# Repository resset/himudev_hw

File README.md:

# hIMUdev

hIMUdev is a RISC-V powered IMU evaluation board. Current version (1.0) hasn't been tested yet, so expect updates and changes.

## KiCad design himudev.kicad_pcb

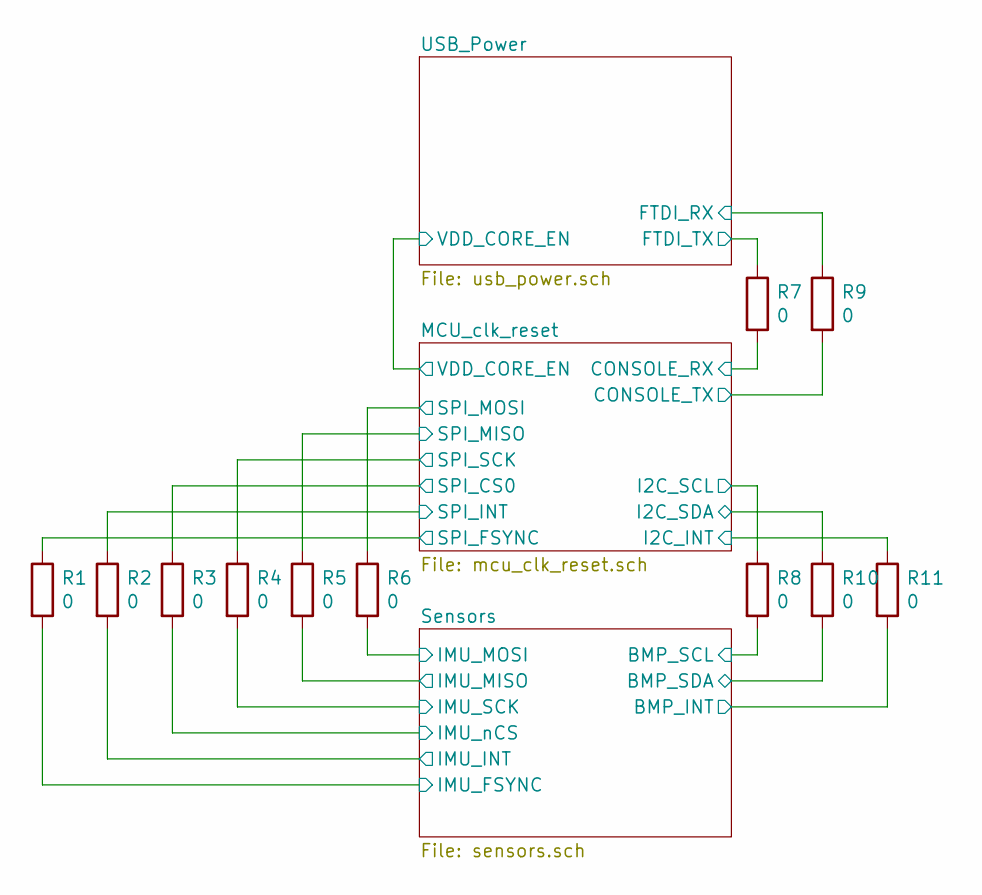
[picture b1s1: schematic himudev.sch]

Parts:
R1, R2, R3, R4, R5, R6, R7, R8, R9, R10, R11: 0; R_0603_1608Metric_Pad1.05x0.95mm_HandSolder

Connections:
/MCU_clk_reset/CONSOLE_RX: R7.2; also elsewhere on the board
/MCU_clk_reset/CONSOLE_TX: R9.2; also elsewhere on the board
/MCU_clk_reset/I2C_INT: R11.1; also elsewhere on the board
/MCU_clk_reset/I2C_SCL: R8.1; also elsewhere on the board
/MCU_clk_reset/I2C_SDA: R10.1; also elsewhere on the board
/MCU_clk_reset/SPI_CS0: R3.1; also elsewhere on the board
/MCU_clk_reset/SPI_FSYNC: R1.1; also elsewhere on the board
/MCU_clk_reset/SPI_INT: R2.1; also elsewhere on the board
/MCU_clk_reset/SPI_MISO: R5.1; also elsewhere on the board
/MCU_clk_reset/SPI_MOSI: R6.1; also elsewhere on the board
/MCU_clk_reset/SPI_SCK: R4.1; also elsewhere on the board
/Sensors/BMP_INT: R11.2; also elsewhere on the board
/Sensors/BMP_SCL: R8.2; also elsewhere on the board
/Sensors/BMP_SDA: R10.2; also elsewhere on the board
/Sensors/IMU_FSYNC: R1.2; also elsewhere on the board
/Sensors/IMU_INT: R2.2; also elsewhere on the board
/Sensors/IMU_MISO: R5.2; also elsewhere on the board
/Sensors/IMU_MOSI: R6.2; also elsewhere on the board
/Sensors/IMU_SCK: R4.2; also elsewhere on the board
/Sensors/IMU_nCS: R3.2; also elsewhere on the board
/USB_Power/FTDI_RX: R9.1; also elsewhere on the board
/USB_Power/FTDI_TX: R7.1; also elsewhere on the board

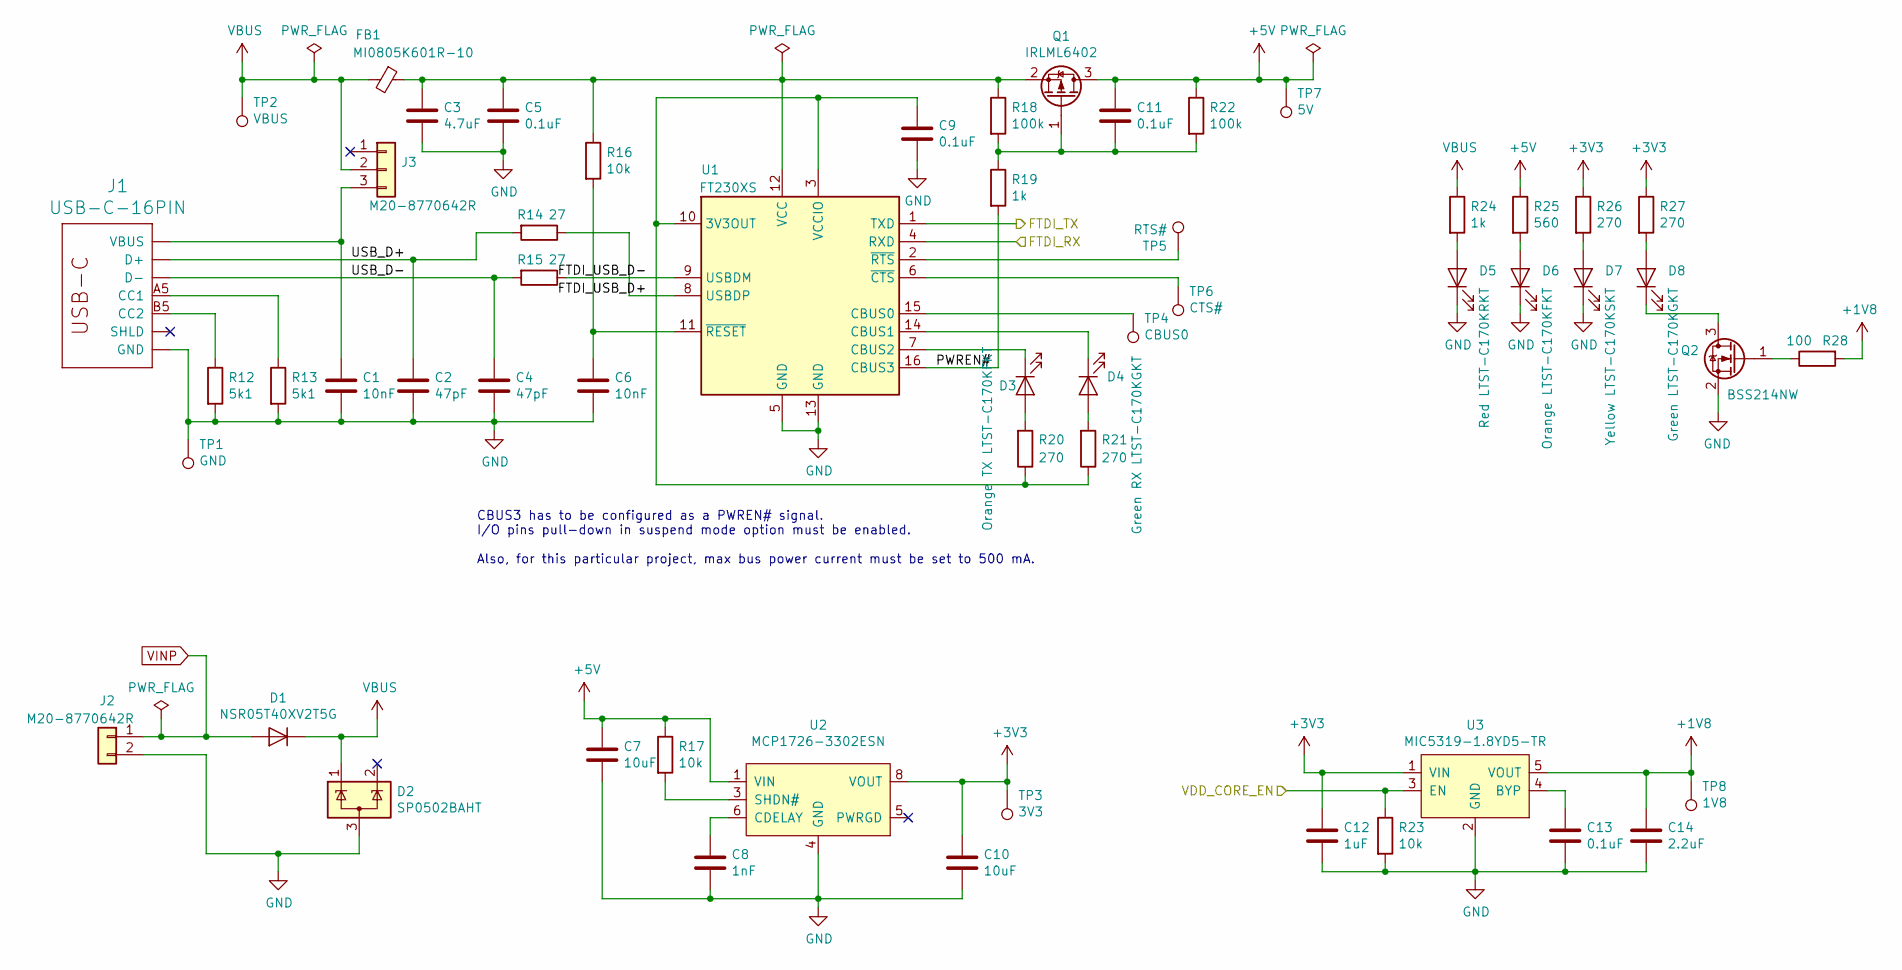
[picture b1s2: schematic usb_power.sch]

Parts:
C1, C6: 10nF; C_0603_1608Metric_Pad1.05x0.95mm_HandSolder
C2, C4: 47pF; C_0603_1608Metric_Pad1.05x0.95mm_HandSolder
C3: 4.7uF; C_0603_1608Metric_Pad1.05x0.95mm_HandSolder
C5, C9, C11, C13: 0.1uF; C_0603_1608Metric_Pad1.05x0.95mm_HandSolder
C7, C10: 10uF; C_0603_1608Metric_Pad1.05x0.95mm_HandSolder
C8: 1nF; C_0603_1608Metric_Pad1.05x0.95mm_HandSolder
C12: 1uF; C_0603_1608Metric_Pad1.05x0.95mm_HandSolder
C14: 2.2uF; C_0603_1608Metric_Pad1.05x0.95mm_HandSolder
D1: NSR05T40XV2T5G; D_SOD-523
D2: SP0502BAHT; SOT-23
D3: Orange TX LTST-C170KFKT; LED_0805_2012Metric_Pad1.15x1.40mm_HandSolder
D4: Green RX LTST-C170KGKT; LED_0805_2012Metric_Pad1.15x1.40mm_HandSolder
D5: Red LTST-C170KRKT; LED_0805_2012Metric_Pad1.15x1.40mm_HandSolder
D6: Orange LTST-C170KFKT; LED_0805_2012Metric_Pad1.15x1.40mm_HandSolder
D7: Yellow LTST-C170KSKT; LED_0805_2012Metric_Pad1.15x1.40mm_HandSolder
D8: Green LTST-C170KGKT; LED_0805_2012Metric_Pad1.15x1.40mm_HandSolder
FB1: MI0805K601R-10; R_0805_2012Metric_Pad1.15x1.40mm_HandSolder
J1: USB-C-16PIN; USB-C-COM-15111
J2: M20-8770642R; PinHeader_1x02_P2.54mm_Vertical_SMD_Pin1Left
J3: M20-8770642R; PinHeader_1x03_P2.54mm_Vertical_SMD_Pin1Left
Q1: IRLML6402; SOT-23
Q2: BSS214NW; SOT-323_SC-70
R12, R13: 5k1; R_0603_1608Metric_Pad1.05x0.95mm_HandSolder
R14, R15: 27; R_0603_1608Metric_Pad1.05x0.95mm_HandSolder
R16, R17, R23: 10k; R_0603_1608Metric_Pad1.05x0.95mm_HandSolder
R18, R22: 100k; R_0603_1608Metric_Pad1.05x0.95mm_HandSolder
R19, R24: 1k; R_0603_1608Metric_Pad1.05x0.95mm_HandSolder
R20, R21, R26, R27: 270; R_0603_1608Metric_Pad1.05x0.95mm_HandSolder
R25: 560; R_0603_1608Metric_Pad1.05x0.95mm_HandSolder
R28: 100; R_0603_1608Metric_Pad1.05x0.95mm_HandSolder
TP1: GND; TestPoint_Pad_D1.5mm
TP2: VBUS; TestPoint_Pad_D1.5mm
TP3: 3V3; TestPoint_Pad_D1.5mm
TP4: CBUS0; TestPoint_Pad_D1.5mm
TP5: RTS#; TestPoint_Pad_D1.5mm
TP6: CTS#; TestPoint_Pad_D1.5mm
TP7: 5V; TestPoint_Pad_D1.5mm
TP8: 1V8; TestPoint_Pad_D1.5mm
U1: FT230XS; SSOP-16_3.9x4.9mm_P0.635mm
U2: MCP1726-3302ESN; SOIC-8_3.9x4.9mm_P1.27mm
U3: MIC5319-1.8YD5-TR; TSOT-23-5

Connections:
+1V8: C14.1, R28.2, TP8.1, U3.5 (VOUT); also elsewhere on the board
+3V3: C10.1, C12.1, R26.1, R27.1, TP3.1, U2.7 (VOUT), U2.8 (VOUT), U3.1 (VIN); also elsewhere on the board
+5V: C7.1, C11.1, Q1.3 (D), R17.1, R22.1, R25.1, TP7.1, U2.1 (VIN), U2.2 (VIN); also elsewhere on the board
/MCU_clk_reset/VDD_CORE_EN: R23.1, U3.3 (EN); also elsewhere on the board
/USB_Power/FTDI_RX: U1.4 (RXD); also elsewhere on the board
/USB_Power/FTDI_TX: U1.1 (TXD); also elsewhere on the board
/USB_Power/FTDI_USB_D+: R14.1, U1.8 (USBDP)
/USB_Power/FTDI_USB_D-: R15.1, U1.9 (USBDM)
/USB_Power/PWREN#: R19.2, U1.16 (CBUS3)
/USB_Power/USB_D+: C2.1, J1.A6 (D+), J1.B6 (D+), R14.2
/USB_Power/USB_D-: C4.1, J1.A7 (D-), J1.B7 (D-), R15.2
GND: C1.2, C2.2, C3.2, C4.2, C5.2, C6.2, C7.2, C8.2, C9.2, C10.2, C12.2, C13.2, C14.2, D2.3 (A), D5.1 (K), D6.1 (K), D7.1 (K), J1.GND, J1.GND2 (GND), J2.2, Q2.2 (S), R12.2, R13.2, R23.2, TP1.1, U1.5 (GND), U1.13 (GND), U2.4 (GND), U3.2 (GND); also elsewhere on the board
unnamed: C1.1, J1.VBUS1 (VBUS), J1.VBUS2 (VBUS), J3.3
unnamed: C3.1, C5.1, FB1.1, Q1.2 (S), R16.1, R18.1, U1.12 (VCC)
unnamed: C6.1, R16.2, U1.11 (~RESET)
unnamed: C8.1, U2.6 (CDELAY)
unnamed: C9.1, R20.1, R21.1, U1.3 (VCCIO), U1.10 (3V3OUT)
unnamed: C11.2, Q1.1 (G), R18.2, R19.1, R22.2
unnamed: C13.1, U3.4 (BYP)
unnamed: D3.1 (K), U1.7 (CBUS2)
unnamed: D3.2 (A), R20.2
unnamed: D4.1 (K), U1.14 (CBUS1)
unnamed: D4.2 (A), R21.2
unnamed: D5.2 (A), R24.2
unnamed: D6.2 (A), R25.2
unnamed: D7.2 (A), R26.2
unnamed: D8.1 (K), Q2.3 (D)
unnamed: D8.2 (A), R27.2
unnamed: J1.A5 (CC1), R13.1
unnamed: J1.B5 (CC2), R12.1
unnamed: J1.SHLD1 (SHLD), J1.SHLD2 (SHLD), J1.SHLD3 (SHLD), J1.SHLD4 (SHLD), J1.SHLD5 (SHLD), J1.SHLD6 (SHLD), J1.SHLD7 (SHLD), J1.SHLD8 (SHLD)
unnamed: Q2.1 (G), R28.1
unnamed: R17.2, U2.3 (SHDN#)
unnamed: TP4.1, U1.15 (CBUS0)
unnamed: TP5.1, U1.2 (~RTS)
unnamed: TP6.1, U1.6 (~CTS)
VBUS: D1.1 (K), D2.1 (K), FB1.2, J3.2, R24.1, TP2.1; also elsewhere on the board
VINP: D1.2 (A), J2.1; also elsewhere on the board

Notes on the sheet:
CBUS3 has to be configured as a PWREN# signal. I/O pins pull-down in suspend mode option must be enabled. Also, for this particular project, max bus power current must be set to 500 mA.

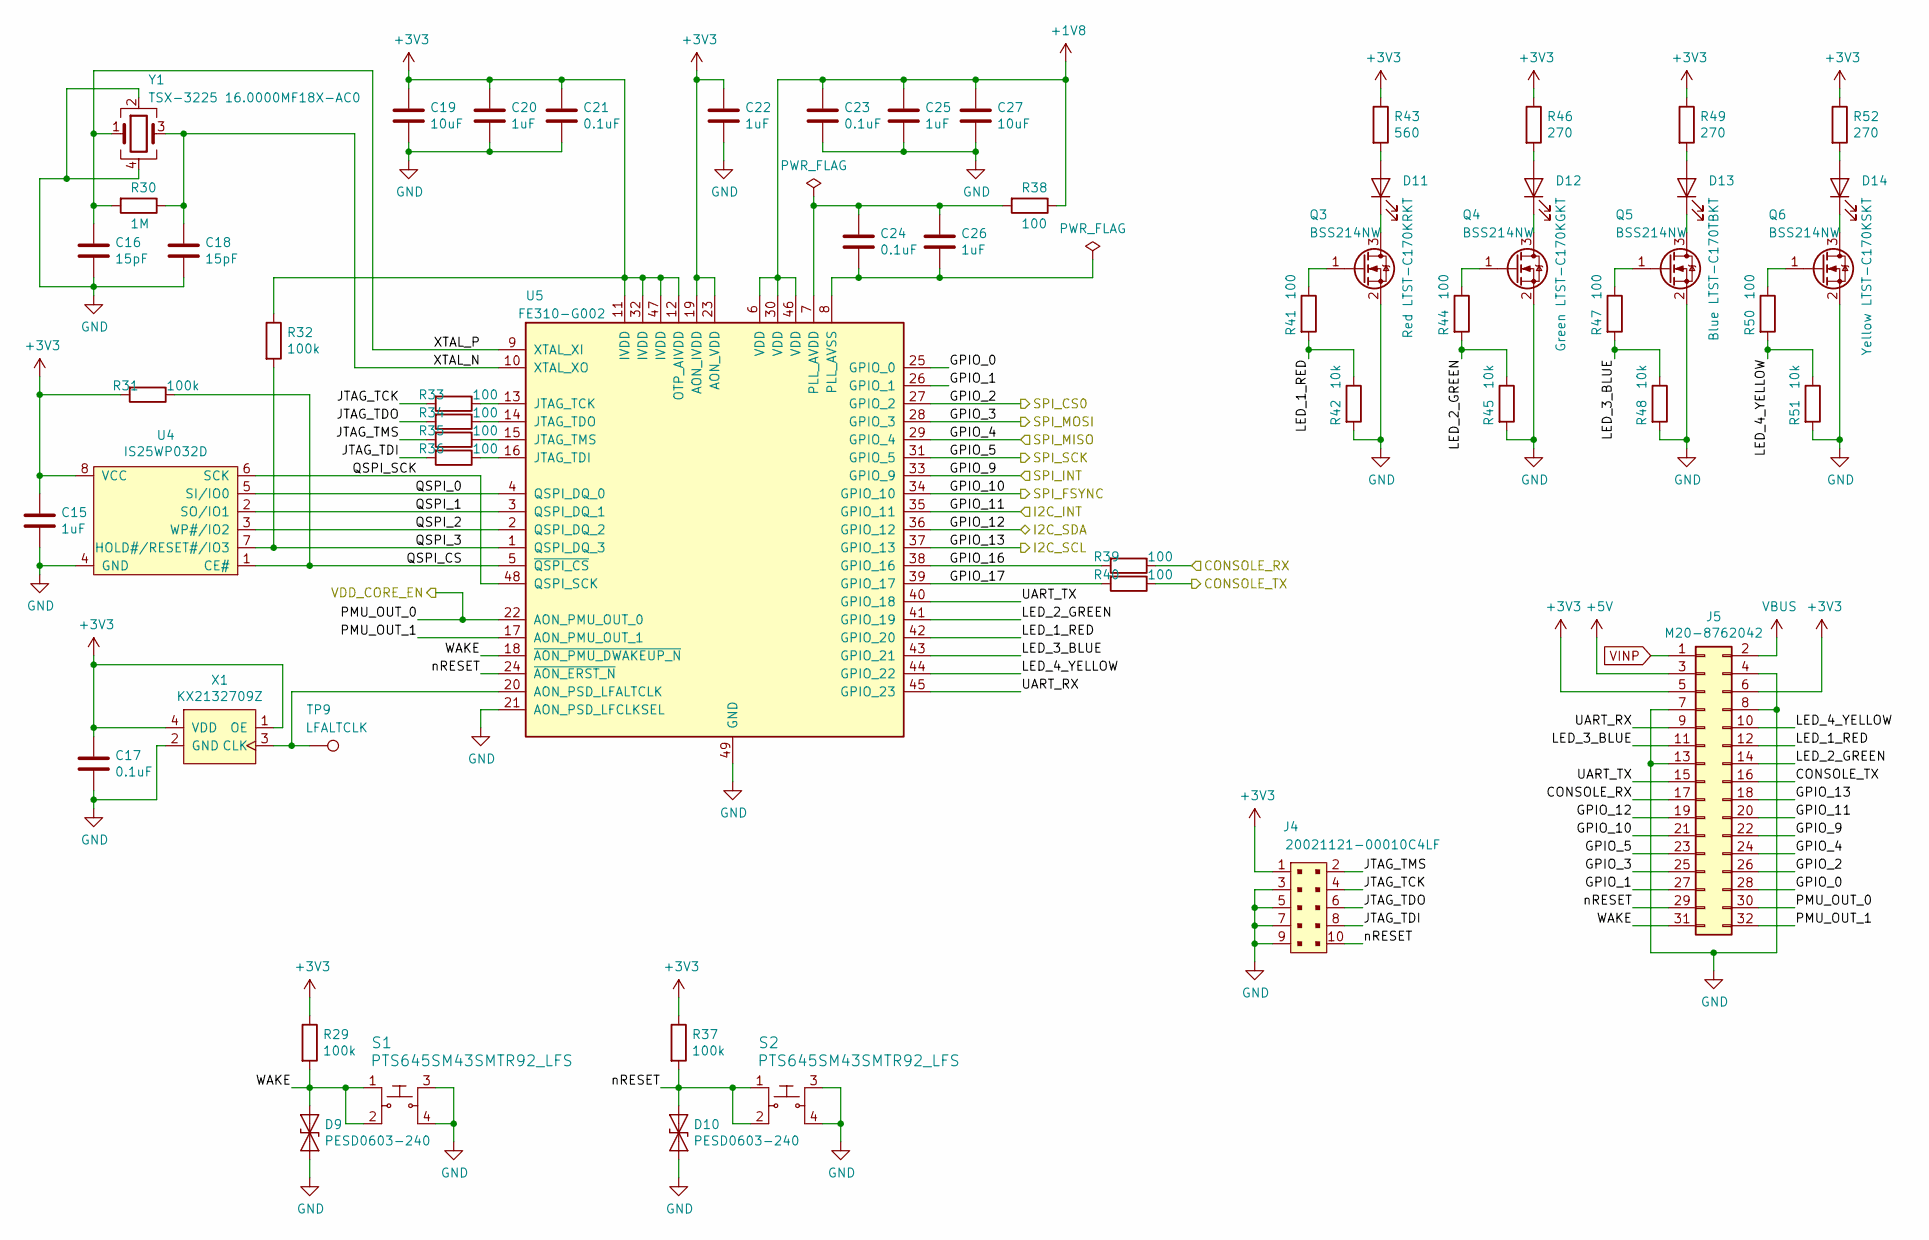
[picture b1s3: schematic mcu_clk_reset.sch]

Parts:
C15, C20, C22, C25, C26: 1uF; C_0603_1608Metric_Pad1.05x0.95mm_HandSolder
C16, C18: 15pF; C_0603_1608Metric_Pad1.05x0.95mm_HandSolder
C17, C21, C23, C24: 0.1uF; C_0603_1608Metric_Pad1.05x0.95mm_HandSolder
C19, C27: 10uF; C_0603_1608Metric_Pad1.05x0.95mm_HandSolder
D9, D10: PESD0603-240; D_0603_1608Metric_Pad1.05x0.95mm_HandSolder
D11: Red LTST-C170KRKT; LED_0805_2012Metric_Pad1.15x1.40mm_HandSolder
D12: Green LTST-C170KGKT; LED_0805_2012Metric_Pad1.15x1.40mm_HandSolder
D13: Blue LTST-C170TBKT; LED_0805_2012Metric_Pad1.15x1.40mm_HandSolder
D14: Yellow LTST-C170KSKT; LED_0805_2012Metric_Pad1.15x1.40mm_HandSolder
J4: 20021121-00010C4LF; PinHeader_2x5_P1.27mm; MPN 20021121-00010C4LF; Digi-Key_PN 609-3695-1-ND
J5: M20-8762042; PinHeader_2x16_P2.54mm_Vertical_SMD
Q3, Q4, Q5, Q6: BSS214NW; SOT-323_SC-70
R29, R31, R32, R37: 100k; R_0603_1608Metric_Pad1.05x0.95mm_HandSolder
R30: 1M; R_0603_1608Metric_Pad1.05x0.95mm_HandSolder
R33, R34, R35, R36, R38, R39, R40, R41, R44, R47, R50: 100; R_0603_1608Metric_Pad1.05x0.95mm_HandSolder
R42, R45, R48, R51: 10k; R_0603_1608Metric_Pad1.05x0.95mm_HandSolder
R43: 560; R_0603_1608Metric_Pad1.05x0.95mm_HandSolder
R46, R49, R52: 270; R_0603_1608Metric_Pad1.05x0.95mm_HandSolder
S1, S2: PTS645SM43SMTR92_LFS; Switch_Tactile_SMD_6x6mm_PTS645; MPN PTS645SM43SMTR92 LFS; Digi-Key_PN CKN9112CT-ND
TP9: LFALTCLK; TestPoint_Pad_D1.5mm
U4: IS25WP032D; SOIC-8_3.9x4.9mm_P1.27mm
U5: FE310-G002; QFN-48-1EP_6x6mm_P0.4mm_EP4.2x4.2mm_BigVia
X1: KX2132709Z
Y1: TSX-3225 16.0000MF18X-AC0; TSX-3225

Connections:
+1V8: C23.1, C25.1, C27.1, R38.1, U5.6 (VDD), U5.30 (VDD), U5.46 (VDD); also elsewhere on the board
+3V3: C15.1, C17.1, C19.1, C20.1, C21.1, C22.1, J4.1, J5.5, J5.6, R29.1, R31.2, R32.1, R37.1, R43.1, R46.1, R49.1, R52.1, U4.8 (VCC), U5.11 (IVDD), U5.12 (OTP_AIVDD), U5.19 (AON_IVDD), U5.23 (AON_VDD), U5.32 (IVDD), U5.47 (IVDD), X1.1 (OE), X1.4 (VDD); also elsewhere on the board
+5V: J5.3; also elsewhere on the board
/MCU_clk_reset/CONSOLE_RX: J5.17, R39.1; also elsewhere on the board
/MCU_clk_reset/CONSOLE_TX: J5.16, R40.1; also elsewhere on the board
/MCU_clk_reset/GPIO_0: J5.28, U5.25 (GPIO_0)
/MCU_clk_reset/GPIO_1: J5.27, U5.26 (GPIO_1)
/MCU_clk_reset/GPIO_16: R39.2, U5.38 (GPIO_16)
/MCU_clk_reset/GPIO_17: R40.2, U5.39 (GPIO_17)
/MCU_clk_reset/I2C_INT: J5.20, U5.35 (GPIO_11); also elsewhere on the board
/MCU_clk_reset/I2C_SCL: J5.18, U5.37 (GPIO_13); also elsewhere on the board
/MCU_clk_reset/I2C_SDA: J5.19, U5.36 (GPIO_12); also elsewhere on the board
/MCU_clk_reset/JTAG_TCK: J4.4, R33.2
/MCU_clk_reset/JTAG_TDI: J4.8, R36.2
/MCU_clk_reset/JTAG_TDO: J4.6, R34.2
/MCU_clk_reset/JTAG_TMS: J4.2, R35.2
/MCU_clk_reset/LED_1_RED: J5.12, R41.2, R42.1, U5.42 (GPIO_20)
/MCU_clk_reset/LED_2_GREEN: J5.14, R44.2, R45.1, U5.41 (GPIO_19)
/MCU_clk_reset/LED_3_BLUE: J5.11, R47.2, R48.1, U5.43 (GPIO_21)
/MCU_clk_reset/LED_4_YELLOW: J5.10, R50.2, R51.1, U5.44 (GPIO_22)
/MCU_clk_reset/PMU_OUT_1: J5.32, U5.17 (AON_PMU_OUT_1)
/MCU_clk_reset/QSPI_0: U4.5 (SI/IO0), U5.4 (QSPI_DQ_0)
/MCU_clk_reset/QSPI_1: U4.2 (SO/IO1), U5.3 (QSPI_DQ_1)
/MCU_clk_reset/QSPI_2: U4.3 (WP#/IO2), U5.2 (QSPI_DQ_2)
/MCU_clk_reset/QSPI_3: R32.2, U4.7 (HOLD#/RESET#/IO3), U5.1 (QSPI_DQ_3)
/MCU_clk_reset/QSPI_CS: R31.1, U4.1 (CE#), U5.5 (~QSPI_CS)
/MCU_clk_reset/QSPI_SCK: U4.6 (SCK), U5.48 (QSPI_SCK)
/MCU_clk_reset/SPI_CS0: J5.26, U5.27 (GPIO_2); also elsewhere on the board
/MCU_clk_reset/SPI_FSYNC: J5.21, U5.34 (GPIO_10); also elsewhere on the board
/MCU_clk_reset/SPI_INT: J5.22, U5.33 (GPIO_9); also elsewhere on the board
/MCU_clk_reset/SPI_MISO: J5.24, U5.29 (GPIO_4); also elsewhere on the board
/MCU_clk_reset/SPI_MOSI: J5.25, U5.28 (GPIO_3); also elsewhere on the board
/MCU_clk_reset/SPI_SCK: J5.23, U5.31 (GPIO_5); also elsewhere on the board
/MCU_clk_reset/UART_RX: J5.9, U5.45 (GPIO_23)
/MCU_clk_reset/UART_TX: J5.15, U5.40 (GPIO_18)
/MCU_clk_reset/VDD_CORE_EN: J5.30, U5.22 (AON_PMU_OUT_0); also elsewhere on the board
/MCU_clk_reset/WAKE: D9.1 (A1), J5.31, R29.2, S1.1, S1.2, U5.18 (~AON_PMU_DWAKEUP_N)
/MCU_clk_reset/XTAL_N: C18.1, R30.1, U5.10 (XTAL_XO), Y1.3
/MCU_clk_reset/XTAL_P: C16.1, R30.2, U5.9 (XTAL_XI), Y1.1
/MCU_clk_reset/nRESET: D10.1 (A1), J4.10, J5.29, R37.2, S2.1, S2.2, U5.24 (~AON_ERST_N)
GND: C15.2, C16.2, C17.2, C18.2, C19.2, C20.2, C21.2, C22.2, C23.2, C25.2, C27.2, D9.2 (A2), D10.2 (A2), J4.3, J4.5, J4.7, J4.9, J5.4, J5.7, J5.8, J5.13, Q3.2 (S), Q4.2 (S), Q5.2 (S), Q6.2 (S), R42.2, R45.2, R48.2, R51.2, S1.3, S1.4, S2.3, S2.4, U4.4 (GND), U5.21 (AON_PSD_LFCLKSEL), U5.49 (GND), X1.2 (GND), Y1.2, Y1.4; also elsewhere on the board
unnamed: C24.1, C26.1, R38.2, U5.7 (PLL_AVDD)
unnamed: C24.2, C26.2, U5.8 (PLL_AVSS)
unnamed: D11.1 (K), Q3.3 (D)
unnamed: D11.2 (A), R43.2
unnamed: D12.1 (K), Q4.3 (D)
unnamed: D12.2 (A), R46.2
unnamed: D13.1 (K), Q5.3 (D)
unnamed: D13.2 (A), R49.2
unnamed: D14.1 (K), Q6.3 (D)
unnamed: D14.2 (A), R52.2
unnamed: Q3.1 (G), R41.1
unnamed: Q4.1 (G), R44.1
unnamed: Q5.1 (G), R47.1
unnamed: Q6.1 (G), R50.1
unnamed: R33.1, U5.13 (JTAG_TCK)
unnamed: R34.1, U5.14 (JTAG_TDO)
unnamed: R35.1, U5.15 (JTAG_TMS)
unnamed: R36.1, U5.16 (JTAG_TDI)
unnamed: TP9.1, U5.20 (AON_PSD_LFALTCLK), X1.3 (CLK)
VBUS: J5.2; also elsewhere on the board
VINP: J5.1; also elsewhere on the board

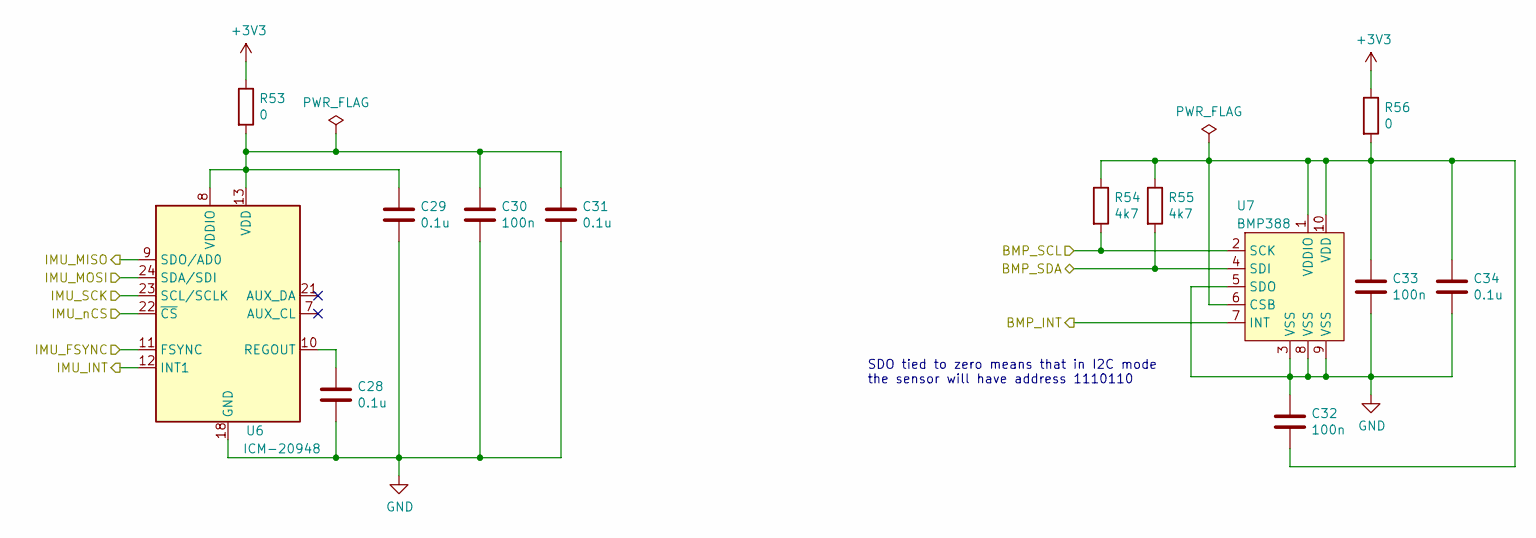
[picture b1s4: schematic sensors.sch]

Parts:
C28, C29, C31, C34: 0.1u; C_0603_1608Metric_Pad1.05x0.95mm_HandSolder
C30, C32, C33: 100n; C_0603_1608Metric_Pad1.05x0.95mm_HandSolder
R53, R56: 0; R_0603_1608Metric_Pad1.05x0.95mm_HandSolder
R54, R55: 4k7; R_0603_1608Metric_Pad1.05x0.95mm_HandSolder
U6: ICM-20948; InvenSense_QFN-24_3x3mm_P0.4mm
U7: BMP388; Bosch_LGA-10_2x2mm_P0.5mm

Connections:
+3V3: R53.1, R56.1; also elsewhere on the board
/Sensors/BMP_INT: U7.7 (INT); also elsewhere on the board
/Sensors/BMP_SCL: R54.2, U7.2 (SCK); also elsewhere on the board
/Sensors/BMP_SDA: R55.2, U7.4 (SDI); also elsewhere on the board
/Sensors/IMU_FSYNC: U6.11 (FSYNC); also elsewhere on the board
/Sensors/IMU_INT: U6.12 (INT1); also elsewhere on the board
/Sensors/IMU_MISO: U6.9 (SDO/AD0); also elsewhere on the board
/Sensors/IMU_MOSI: U6.24 (SDA/SDI); also elsewhere on the board
/Sensors/IMU_SCK: U6.23 (SCL/SCLK); also elsewhere on the board
/Sensors/IMU_nCS: U6.22 (~CS); also elsewhere on the board
GND: C28.2, C29.2, C30.2, C31.2, C32.1, C33.2, C34.2, U6.18 (GND), U6.20 (GND), U7.3 (VSS), U7.5 (SDO), U7.8 (VSS), U7.9 (VSS); also elsewhere on the board
unnamed: C28.1, U6.10 (REGOUT)
unnamed: C29.1, C30.1, C31.1, R53.2, U6.8 (VDDIO), U6.13 (VDD)
unnamed: C32.2, C33.1, C34.1, R54.1, R55.1, R56.2, U7.1 (VDDIO), U7.6 (CSB), U7.10 (VDD)

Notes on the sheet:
SDO tied to zero means that in I2C mode the sensor will have address 1110110

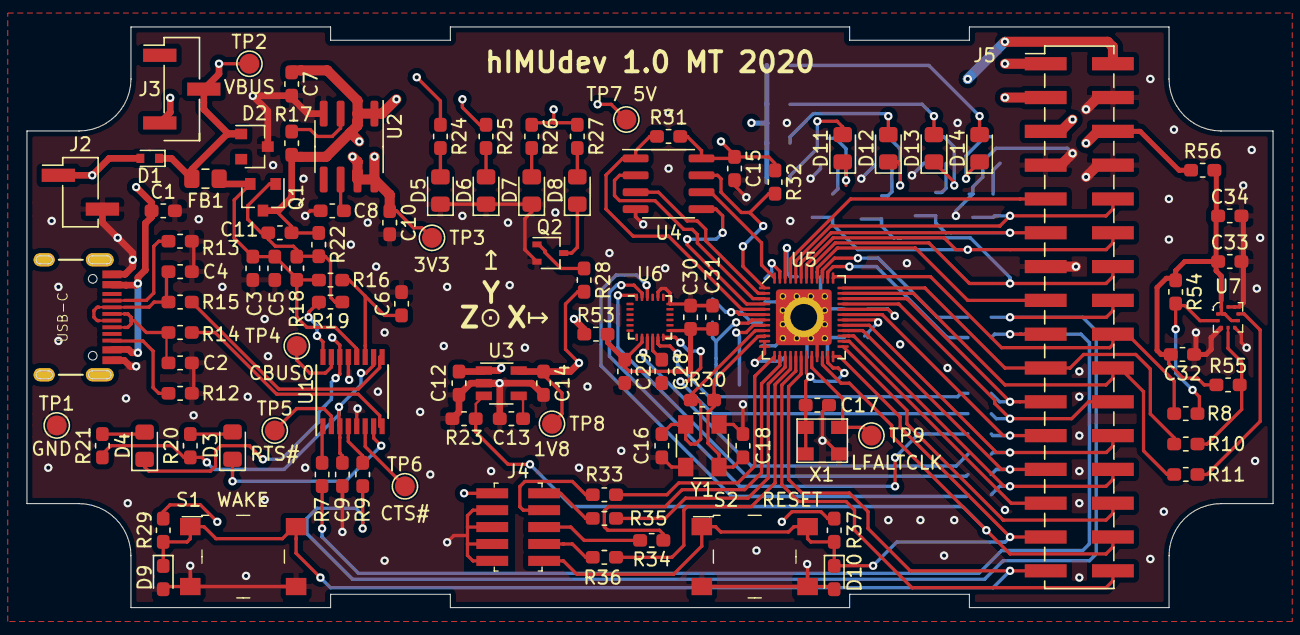
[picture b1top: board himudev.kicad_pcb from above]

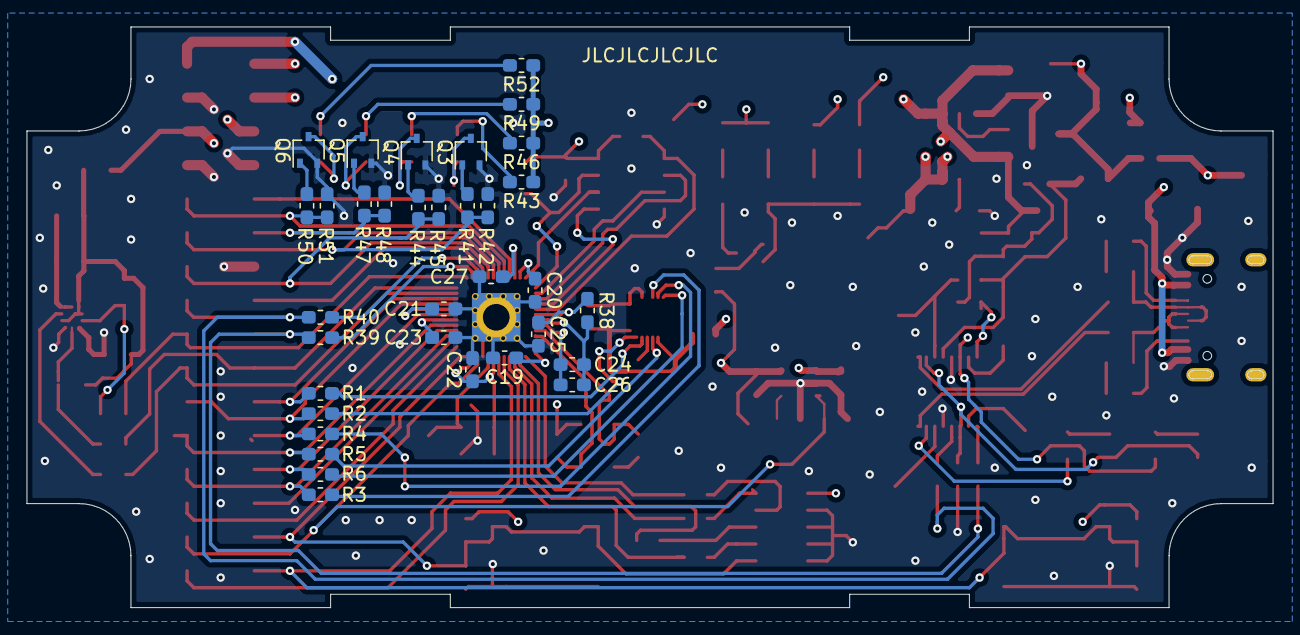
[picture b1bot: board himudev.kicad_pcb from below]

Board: 4 copper layers, 93.6 x 43.6 mm, 136 parts (34 on the bottom side), 105 nets.

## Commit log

2019-12-22 Initial commit
    Power & clock section mostly done, MCU present.
2019-12-22 Update LEDs descriptions, add main osc footprint
2019-12-22 Change main MCU footprint
    Now it has a big hole in the back which will help me connecting it to GND
    with a soldering iron.
2019-12-22 Select footprint for main osc
2019-12-22 Add QSPI flash
2020-01-13 First full version of a schematic
    This commit is a quicksave of completed but not reviewed schematic.
    Added pressure sensor, finished IMU wiring, finished top-level
    schematic, added pin header, placed LEDs and many others.
2020-01-13 Moved some schematics around, no real changes
2020-01-13 Add ERC fixes, mostly PWR_FLAGs
    Also, fixed MCP1726 symbol.
2020-01-13 Assigned footprints, generated netlist
    I can already see some footprints issues. Eg. the switches have to be
    changed to the SMT version. There are some silkscreen issues in custom
    oscillator footprints. Otherwise looks promising :)
2020-01-13 Change board to four-layer one
2020-01-14 Fix silkscreen on himudev footprints
2020-01-14 Change tactile switches to PTS645
2020-01-14 Reload netlist, set part number of J1 and J3
2020-01-15 Placed component footprints in logical groups
2020-01-16 Changed main header from 34 to 32 pin, added board outline
2020-02-01 Placed pressure sensor, connector changed to USB-C
2020-02-01 Route power traces on the inner layer
2020-02-02 Add board cutouts (enclosure features)
    Also, more placement of the components done.
2020-02-05 Remap main header pins
    Allows for better use of board estate.
2020-02-08 Re-annotated all elements
    This is a step to prepare for a change from 0805 to 0603 components. Not
    critical but nice to have them in order.
2020-03-05 Use 0603 components, on both sides, route header
    This decision was due to the current placement overcrowded and to the
    fact that successful routing on one side was uncertain.
2020-03-06 Placed MCU decoupling capacitors
2020-03-06 Placed everything apart from FTDI
2020-03-06 FTDI placement proposal, not connected yet
2020-03-06 Finished routing
    Yay!
2020-03-06 Small via & silkscreen fixes
2020-03-06 Add JLCPCB SN placeholder, fix silkscreen
2020-03-06 Export Gerber and drill files
2020-03-07 Made testpoint silkscreen more readable
    Also, regenerated Gerber files.
2020-03-07 Added README
2020-04-06 Fix labels placement on the schematics
2020-04-06 .gitignore: do not track KiBoM ini file
2020-04-06 Added TODO with a list of changes. Not final.
    The good news is that 75% of the board works, the rest is not tested
    yet. Things to check:
    - IMU
    - BMP
2020-04-06 Add ned TODOs
2020-04-06 Reorder power LEDs in schematics, fix some USB-C DRC errors
2020-04-06 Close first TODO task
2020-04-06 Fix: exchange FTDI TX and RX diode colors
2020-04-08 Fix FTDI RX/TX diode designator
2020-04-08 Add TODOs
2020-04-11 Change resistor values to adjust LED brightness
2020-04-13 Add 10k pull-downs on MCU LED outputs, improve layout
    Pushed few traces, fixed DRC issue on one of the vias.
2020-04-13 Switch places of D3 and D4
    Also, fixed 1V8 via placement.
2020-04-13 Move J4 up by 1 mm, add copper keepout around GND pins
2020-04-16 Tidy up schematics a bit
2020-04-16 Reject one task from TODO
2020-04-16 Rejest Y1 rotation, add trace length TODO
2020-04-21 Add magnificent InteractiveHtmlBom BOM
2020-04-28 Add nets and tracks to the HTML BOM
2020-05-09 Add testpoints labels
2020-05-09 Add labels for buttons
2020-05-10 Change ICM-20948 supply from 1V8 to 3V3
2020-05-10 Update HTML BOM
2020-05-10 Update TODO
2020-05-11 TODO: add IMU voltage level translators task
    This is something I overlooked and a bug in a schematics. GPIOs of the
    IMU work in 1V8 domain only so some kind of level translation is needed.
    And it should land close to the IMU itself, so the J5 stays in the 3V3
    domain.
